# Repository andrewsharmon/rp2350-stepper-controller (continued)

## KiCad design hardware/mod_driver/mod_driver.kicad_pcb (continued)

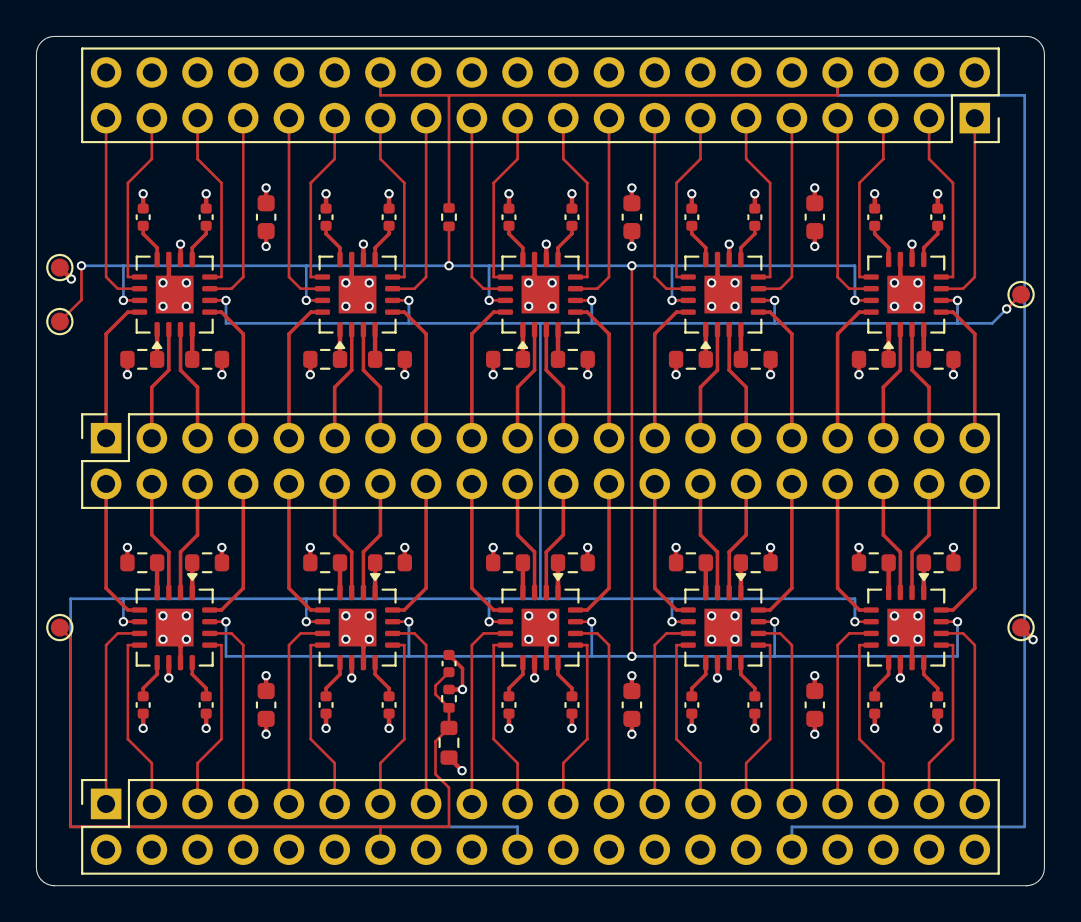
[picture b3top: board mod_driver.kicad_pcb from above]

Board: 4 copper layers, 56.0 x 47.2 mm, 68 parts (0 on the bottom side), 126 nets.

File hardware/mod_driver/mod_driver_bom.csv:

"Refs","Value","Footprint","Qty","MPN","LCSC","Note"
"C1,C4,C6,C9,C11,C14,C17,C19,C22,C24","1u","Capacitor_SMD:C_0402_1005Metric","10","CL05A105KA5NQNC","C52923",""
"C2,C5,C7,C10,C12,C15,C18,C20,C23,C25,C27","100n","Capacitor_SMD:C_0402_1005Metric","11","CL05B104KO5NNNC","C1525",""
"C3,C8,C13,C16,C21,C26","10u","Capacitor_SMD:C_0603_1608Metric","6","CL10A106KP8NNNC","C19702","VM, shared by the neighbouring drivers in the row; also the V5 bulk"
"J1","2x20 stacking","Connector_PinSocket_2.54mm:PinSocket_2x20_P2.54mm_Vertical","1","2.54-2*20PFemale longPC104","C35165","mod bus A (GPIO0-19 = M1-M5); passes through"
"J2","2x20 stacking","Connector_PinSocket_2.54mm:PinSocket_2x20_P2.54mm_Vertical","1","2.54-2*20PFemale longPC104","C35165","mod bus B (GPIO20-47); passes through"
"J3","2x20 stacking","Connector_PinSocket_2.54mm:PinSocket_2x20_P2.54mm_Vertical","1","2.54-2*20PFemale longPC104","C35165","motor outputs to mod_motor"
"R1-R20","1","Resistor_SMD:R_0603_1608Metric","20","0603WAF100KT5E","C22936","chops at 0.16-0.24 A (VTRIP 160-240 mV); Kelvin return"
"R21","47k","Resistor_SMD:R_0402_1005Metric","1","0402WGF4702TCE","C25792",""
"R22","39k 1%","Resistor_SMD:R_0603_1608Metric","1","0603WAF3902T5E","C23153",""
"R23","10k 1%","Resistor_SMD:R_0402_1005Metric","1","0402WGF1002TCE","C25744",""
"U1-U10","AT8833CQ","Package_DFN_QFN:QFN-16-1EP_4x4mm_P0.65mm_EP2.1x2.1mm","10","AT8833CQ","C5120769","DRV8833RTY pinout; 2nd source JSMSEMI DRV8833RTYR-JSM C55566425"

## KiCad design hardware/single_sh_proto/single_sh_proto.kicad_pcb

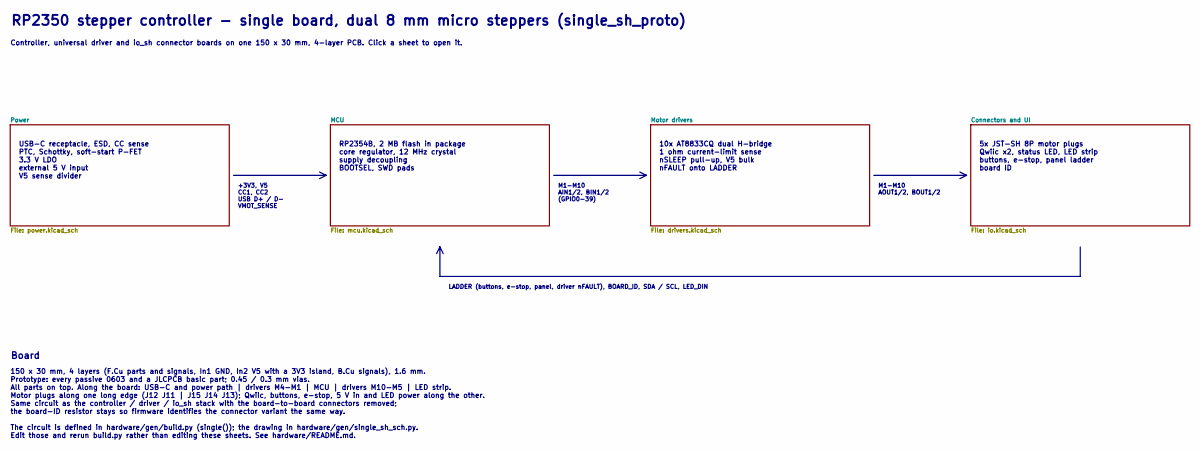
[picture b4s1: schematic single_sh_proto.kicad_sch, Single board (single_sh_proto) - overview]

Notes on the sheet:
RP2350 stepper controller - single board, dual 8 mm micro steppers (single_sh_proto)
Controller, universal driver and io_sh connector boards on one 150 x 30 mm, 4-layer PCB. Click a sheet to open it.
USB-C receptacle, ESD, CC sense PTC, Schottky, soft-start P-FET 3.3 V LDO external 5 V input V5 sense divider
RP2354B, 2 MB flash in package core regulator, 12 MHz crystal supply decoupling BOOTSEL, SWD pads
10x AT8833CQ dual H-bridge 1 ohm current-limit sense nSLEEP pull-up, V5 bulk nFAULT onto LADDER
5x JST-SH 8P motor plugs Qwiic x2, status LED, LED strip buttons, e-stop, panel ladder board ID
+3V3, V5 CC1, CC2 USB D+ / D- VMOT_SENSE
M1-M10 AIN1/2, BIN1/2 (GPIO0-39)
M1-M10 AOUT1/2, BOUT1/2
LADDER (buttons, e-stop, panel, driver nFAULT), BOARD_ID, SDA / SCL, LED_DIN
Board
150 x 30 mm, 4 layers (F.Cu parts and signals, In1 GND, In2 V5 with a 3V3 island, B.Cu signals), 1.6 mm. Prototype: every passive 0603 and a JLCPCB basic part; 0.45 / 0.3 mm vias. All parts on top. Along the board: USB-C and power path | drivers M4-M1 | MCU | drivers M10-M5 | LED strip. Motor plugs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

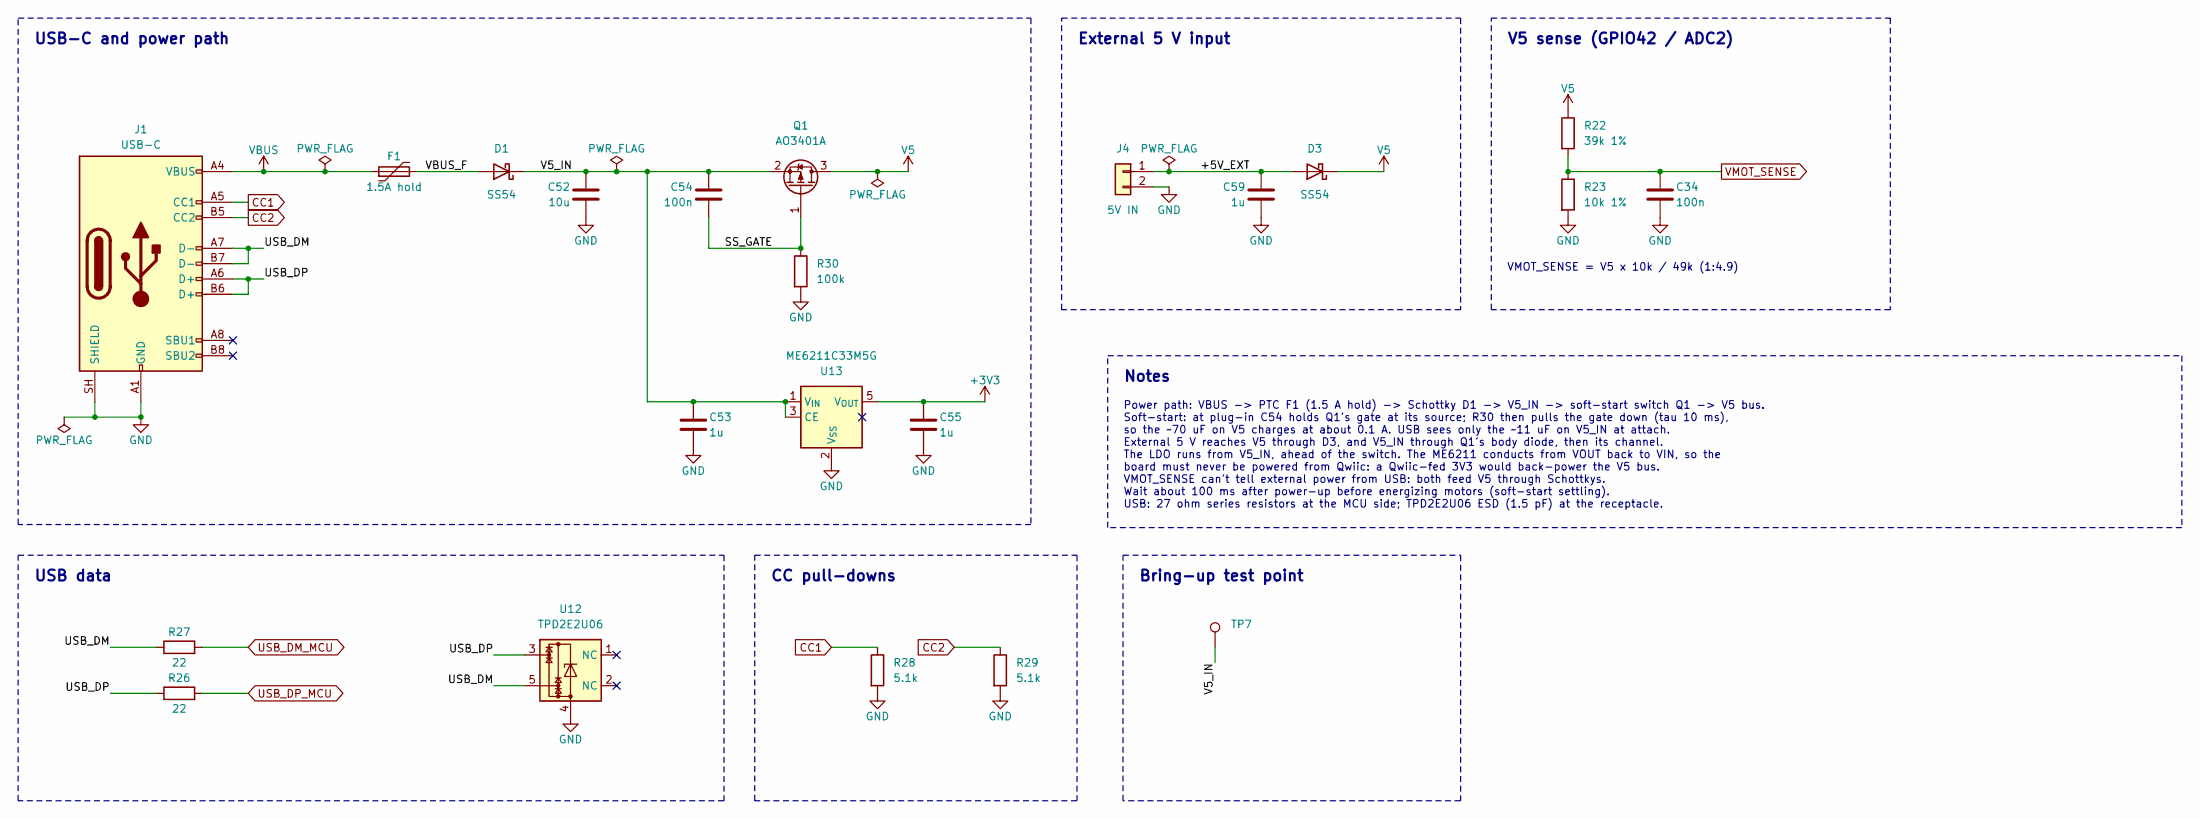
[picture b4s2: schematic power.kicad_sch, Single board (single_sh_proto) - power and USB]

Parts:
C34, C54: 100n; C_0603_1608Metric; MPN CC0603KRX7R9BB104; LCSC C14663
C52: 10u; C_0603_1608Metric; MPN CL10A106KP8NNNC; LCSC C19702
C53, C55, C59: 1u; C_0603_1608Metric; MPN CL10A105KB8NNNC; LCSC C15849
D1, D3: SS54; D_SMA; MPN SS54; LCSC C22452
F1: 1.5A hold; Fuse_1812_4532Metric; MPN SMD1812P150TF/8; LCSC C209721
J1: USB-C; USB_C_Receptacle_HRO_TYPE-C-31-M-12; MPN TYPE-C-31-M-12; LCSC C165948
J4: 5V IN; JST_PH_B2B-PH-K_1x02_P2.00mm_Vertical; MPN B2B-PH-K-S; LCSC C131337
Q1: AO3401A; SOT-23; MPN AO3401A; LCSC C15127
R22: 39k 1%; R_0603_1608Metric; MPN 0603WAF3902T5E; LCSC C23153
R23: 10k 1%; R_0603_1608Metric; MPN 0603WAF1002T5E; LCSC C25804
R26, R27: 22; R_0603_1608Metric; MPN 0603WAF220JT5E; LCSC C23345
R28, R29: 5.1k; R_0603_1608Metric; MPN 0603WAF5101T5E; LCSC C23186
R30: 100k; R_0603_1608Metric; MPN 0603WAF1003T5E; LCSC C25803
TP7: V5_IN; TestPoint_Pad_D1.0mm
U12: TPD2E2U06; SOT-553; MPN TPD2E2U06DRLR; LCSC C1972959
U13: ME6211C33M5G; SOT-23-5; MPN ME6211C33M5G-N; LCSC C82942

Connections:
+3V3: C55.1, U13.5 (V_{OUT}); also elsewhere on the board
/Power/+5V_EXT: C59.1, D3.2 (A), J4.1
/Power/SS_GATE: C54.2, Q1.1 (G), R30.1
/Power/USB_DM: J1.A7 (D-), J1.B7 (D-), R27.1, U12.5
/Power/USB_DP: J1.A6 (D+), J1.B6 (D+), R26.1, U12.3
/Power/V5_IN: C52.1, C53.1, C54.1, D1.1 (K), Q1.2 (S), TP7.1, U13.1 (V_{IN}), U13.3 (CE)
/Power/VBUS_F: D1.2 (A), F1.2
CC1: J1.A5 (CC1), R28.1; also elsewhere on the board
CC2: J1.B5 (CC2), R29.1; also elsewhere on the board
GND: C34.2, C52.2, C53.2, C55.2, C59.2, J1.A1 (GND), J1.A12 (GND), J1.B1 (GND), J1.B12 (GND), J1.SH (SHIELD), J4.2, R23.2, R28.2, R29.2, R30.2, U12.4, U13.2 (V_{SS}); also elsewhere on the board
USB_DM_MCU: R27.2; also elsewhere on the board
USB_DP_MCU: R26.2; also elsewhere on the board
V5: D3.1 (K), Q1.3 (D), R22.1; also elsewhere on the board
VBUS: F1.1, J1.A4 (VBUS), J1.A9 (VBUS), J1.B4 (VBUS), J1.B9 (VBUS); also elsewhere on the board
VMOT_SENSE: C34.1, R22.2, R23.1; also elsewhere on the board

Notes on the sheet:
USB-C and power path
USB data
CC pull-downs
External 5 V input
V5 sense (GPIO42 / ADC2)
VMOT_SENSE = V5 x 10k / 49k (1:4.9)
Notes
Power path: VBUS -> PTC F1 (1.5 A hold) -> Schottky D1 -> V5_IN -> soft-start switch Q1 -> V5 bus. Soft-start: at plug-in C54 holds Q1's gate at its source; R30 then pulls the gate down (tau 10 ms), so the ~70 uF on V5 charges at about 0.1 A. USB sees only the ~11 uF on V5_IN at attach. External 5 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
Bring-up test point

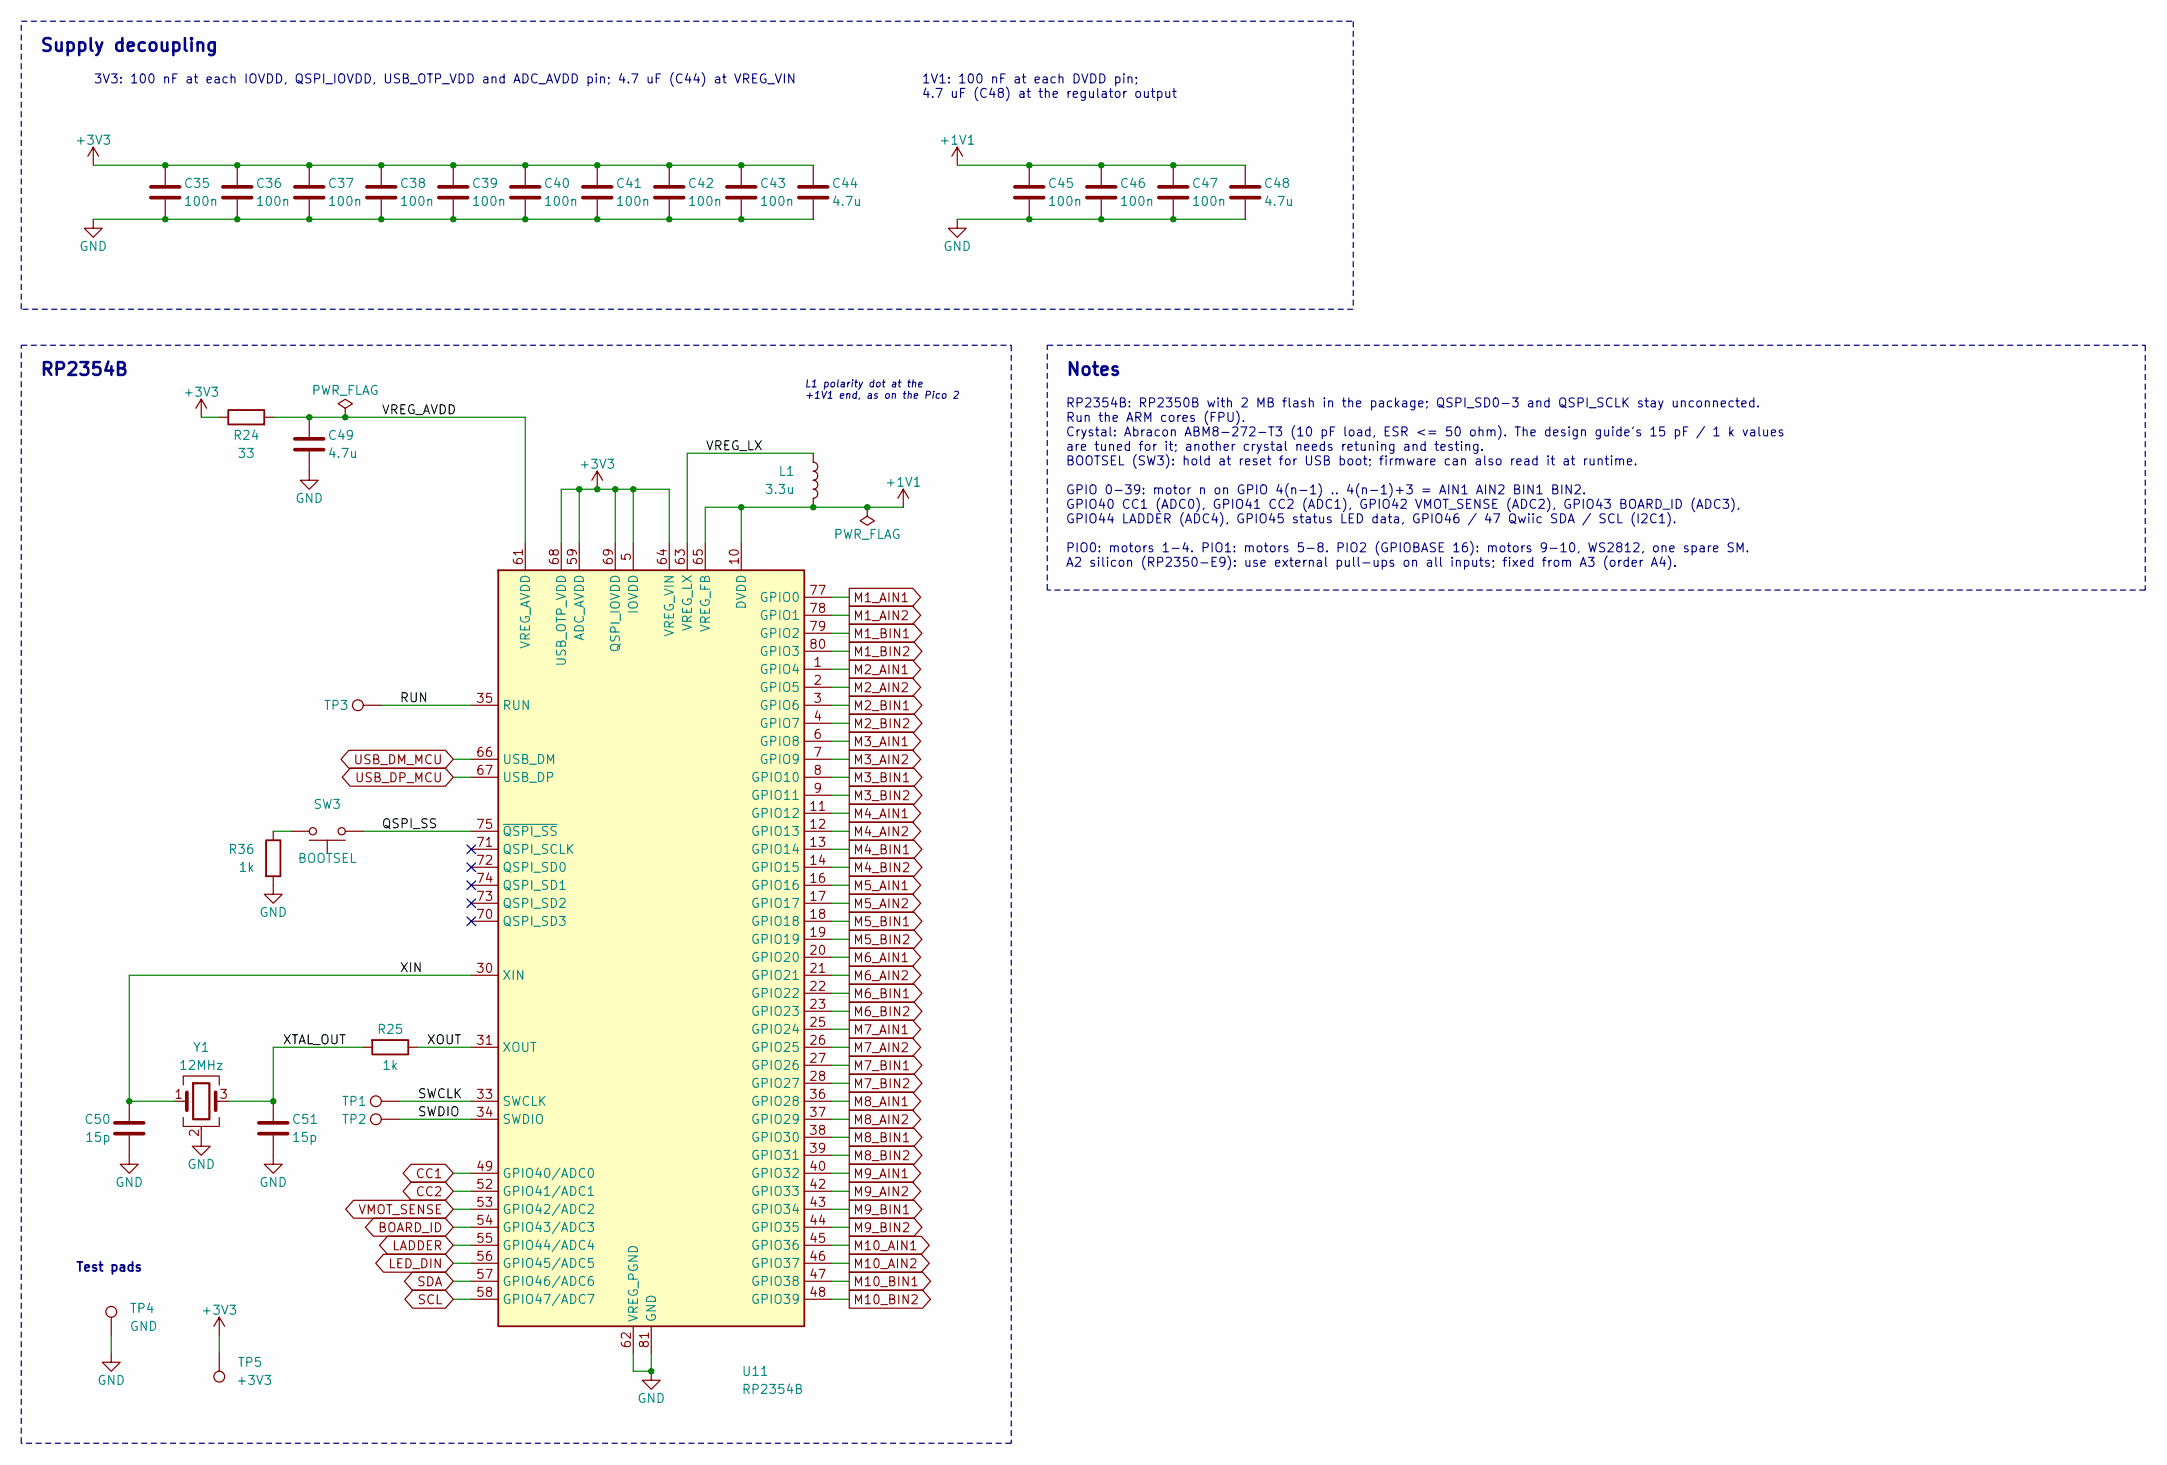
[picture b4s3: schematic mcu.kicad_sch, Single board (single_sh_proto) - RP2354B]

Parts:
C35, C36, C37, C38, C39, C40, C41, C42, C43, C45, C46, C47: 100n; C_0603_1608Metric; MPN CC0603KRX7R9BB104; LCSC C14663
C44, C48, C49: 4.7u; C_0603_1608Metric; MPN CL10A475KO8NNNC; LCSC C19666
C50, C51: 15p; C_0603_1608Metric; MPN CL10C150JB8NNNC; LCSC C1644
L1: 3.3u; L_Cenker_CKCS201610; MPN CMLW201610S3R3MST; LCSC C411344
R24: 33; R_0603_1608Metric; MPN 0603WAF330JT5E; LCSC C23140
R25, R36: 1k; R_0603_1608Metric; MPN 0603WAF1001T5E; LCSC C21190
SW3: BOOTSEL; SW_SPST_TS-1088-xR020; MPN TS-1088-AR02016; LCSC C720477
TP1: SWCLK; TestPoint_Pad_D1.0mm
TP2: SWDIO; TestPoint_Pad_D1.0mm
TP3: RUN; TestPoint_Pad_D1.0mm
TP4: GND; TestPoint_Pad_D1.0mm
TP5: +3V3; TestPoint_Pad_D1.0mm
U11: RP2354B; QFN-80-1EP_10x10mm_P0.4mm_EP3.4x3.4mm; MPN RP2354B; LCSC C39843328
Y1: 12MHz; Crystal_SMD_3225-4Pin_3.2x2.5mm; MPN ABM8-272-T3; LCSC C20625731

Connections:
+1V1: C45.1, C46.1, C47.1, C48.1, L1.2, U11.10 (DVDD), U11.32 (DVDD), U11.51 (DVDD), U11.65 (VREG_FB); also elsewhere on the board
+3V3: C35.1, C36.1, C37.1, C38.1, C39.1, C40.1, C41.1, C42.1, C43.1, C44.1, R24.1, TP5.1, U11.5 (IOVDD), U11.15 (IOVDD), U11.24 (IOVDD), U11.29 (IOVDD), U11.41 (IOVDD), U11.50 (IOVDD), U11.59 (ADC_AVDD), U11.60 (IOVDD), U11.64 (VREG_VIN), U11.68 (USB_OTP_VDD), U11.69 (QSPI_IOVDD), U11.76 (IOVDD); also elsewhere on the board
/MCU/QSPI_SS: SW3.1, U11.75 (~QSPI_SS)
/MCU/RUN: TP3.1, U11.35 (RUN)
/MCU/SWCLK: TP1.1, U11.33 (SWCLK)
/MCU/SWDIO: TP2.1, U11.34 (SWDIO)
/MCU/VREG_AVDD: C49.1, R24.2, U11.61 (VREG_AVDD)
/MCU/VREG_LX: L1.1, U11.63 (VREG_LX)
/MCU/XIN: C50.1, U11.30 (XIN), Y1.1
/MCU/XOUT: R25.1, U11.31 (XOUT)
/MCU/XTAL_OUT: C51.1, R25.2, Y1.3
BOARD_ID: U11.54 (GPIO43/ADC3); also elsewhere on the board
CC1: U11.49 (GPIO40/ADC0); also elsewhere on the board
CC2: U11.52 (GPIO41/ADC1); also elsewhere on the board
GND: C35.2, C36.2, C37.2, C38.2, C39.2, C40.2, C41.2, C42.2, C43.2, C44.2, C45.2, C46.2, C47.2, C48.2, C49.2, C50.2, C51.2, R36.2, TP4.1, U11.62 (VREG_PGND), U11.81 (GND), Y1.2 (G), Y1.4 (G); also elsewhere on the board
LADDER: U11.55 (GPIO44/ADC4); also elsewhere on the board
LED_DIN: U11.56 (GPIO45/ADC5); also elsewhere on the board
M1_AIN1: U11.77 (GPIO0); also elsewhere on the board
M1_AIN2: U11.78 (GPIO1); also elsewhere on the board
M1_BIN1: U11.79 (GPIO2); also elsewhere on the board
M1_BIN2: U11.80 (GPIO3); also elsewhere on the board
M2_AIN1: U11.1 (GPIO4); also elsewhere on the board
M2_AIN2: U11.2 (GPIO5); also elsewhere on the board
M2_BIN1: U11.3 (GPIO6); also elsewhere on the board
M2_BIN2: U11.4 (GPIO7); also elsewhere on the board
M3_AIN1: U11.6 (GPIO8); also elsewhere on the board
M3_AIN2: U11.7 (GPIO9); also elsewhere on the board
M3_BIN1: U11.8 (GPIO10); also elsewhere on the board
M3_BIN2: U11.9 (GPIO11); also elsewhere on the board
M4_AIN1: U11.11 (GPIO12); also elsewhere on the board
M4_AIN2: U11.12 (GPIO13); also elsewhere on the board
M4_BIN1: U11.13 (GPIO14); also elsewhere on the board
M4_BIN2: U11.14 (GPIO15); also elsewhere on the board
M5_AIN1: U11.16 (GPIO16); also elsewhere on the board
M5_AIN2: U11.17 (GPIO17); also elsewhere on the board
M5_BIN1: U11.18 (GPIO18); also elsewhere on the board
M5_BIN2: U11.19 (GPIO19); also elsewhere on the board
M6_AIN1: U11.20 (GPIO20); also elsewhere on the board
M6_AIN2: U11.21 (GPIO21); also elsewhere on the board
M6_BIN1: U11.22 (GPIO22); also elsewhere on the board
M6_BIN2: U11.23 (GPIO23); also elsewhere on the board
M7_AIN1: U11.25 (GPIO24); also elsewhere on the board
M7_AIN2: U11.26 (GPIO25); also elsewhere on the board
M7_BIN1: U11.27 (GPIO26); also elsewhere on the board
M7_BIN2: U11.28 (GPIO27); also elsewhere on the board
M8_AIN1: U11.36 (GPIO28); also elsewhere on the board
M8_AIN2: U11.37 (GPIO29); also elsewhere on the board
M8_BIN1: U11.38 (GPIO30); also elsewhere on the board
M8_BIN2: U11.39 (GPIO31); also elsewhere on the board
M9_AIN1: U11.40 (GPIO32); also elsewhere on the board
M9_AIN2: U11.42 (GPIO33); also elsewhere on the board
M9_BIN1: U11.43 (GPIO34); also elsewhere on the board
M9_BIN2: U11.44 (GPIO35); also elsewhere on the board
M10_AIN1: U11.45 (GPIO36); also elsewhere on the board
M10_AIN2: U11.46 (GPIO37); also elsewhere on the board
M10_BIN1: U11.47 (GPIO38); also elsewhere on the board
M10_BIN2: U11.48 (GPIO39); also elsewhere on the board
unnamed: R36.1, SW3.2
SCL: U11.58 (GPIO47/ADC7); also elsewhere on the board
SDA: U11.57 (GPIO46/ADC6); also elsewhere on the board
USB_DM_MCU: U11.66 (USB_DM); also elsewhere on the board
USB_DP_MCU: U11.67 (USB_DP); also elsewhere on the board
VMOT_SENSE: U11.53 (GPIO42/ADC2); also elsewhere on the board

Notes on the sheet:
RP2354B
L1 polarity dot at the +1V1 end, as on the Pico 2
Supply decoupling
3V3: 100 nF at each IOVDD, QSPI_IOVDD, USB_OTP_VDD and ADC_AVDD pin; 4.7 uF (C44) at VREG_VIN
1V1: 100 nF at each DVDD pin; 4.7 uF (C48) at the regulator output
Test pads
Notes
RP2354B: RP2350B with 2 MB flash in the package; QSPI_SD0-3 and QSPI_SCLK stay unconnected. Run the ARM cores (FPU). Crystal: Abracon ABM8-272-T3 (10 pF load, ESR <= 50 ohm). The design guide's 15 pF / 1 k values are tuned for it; another crystal needs retuning and testing. BOOTSEL (SW3): hold at r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

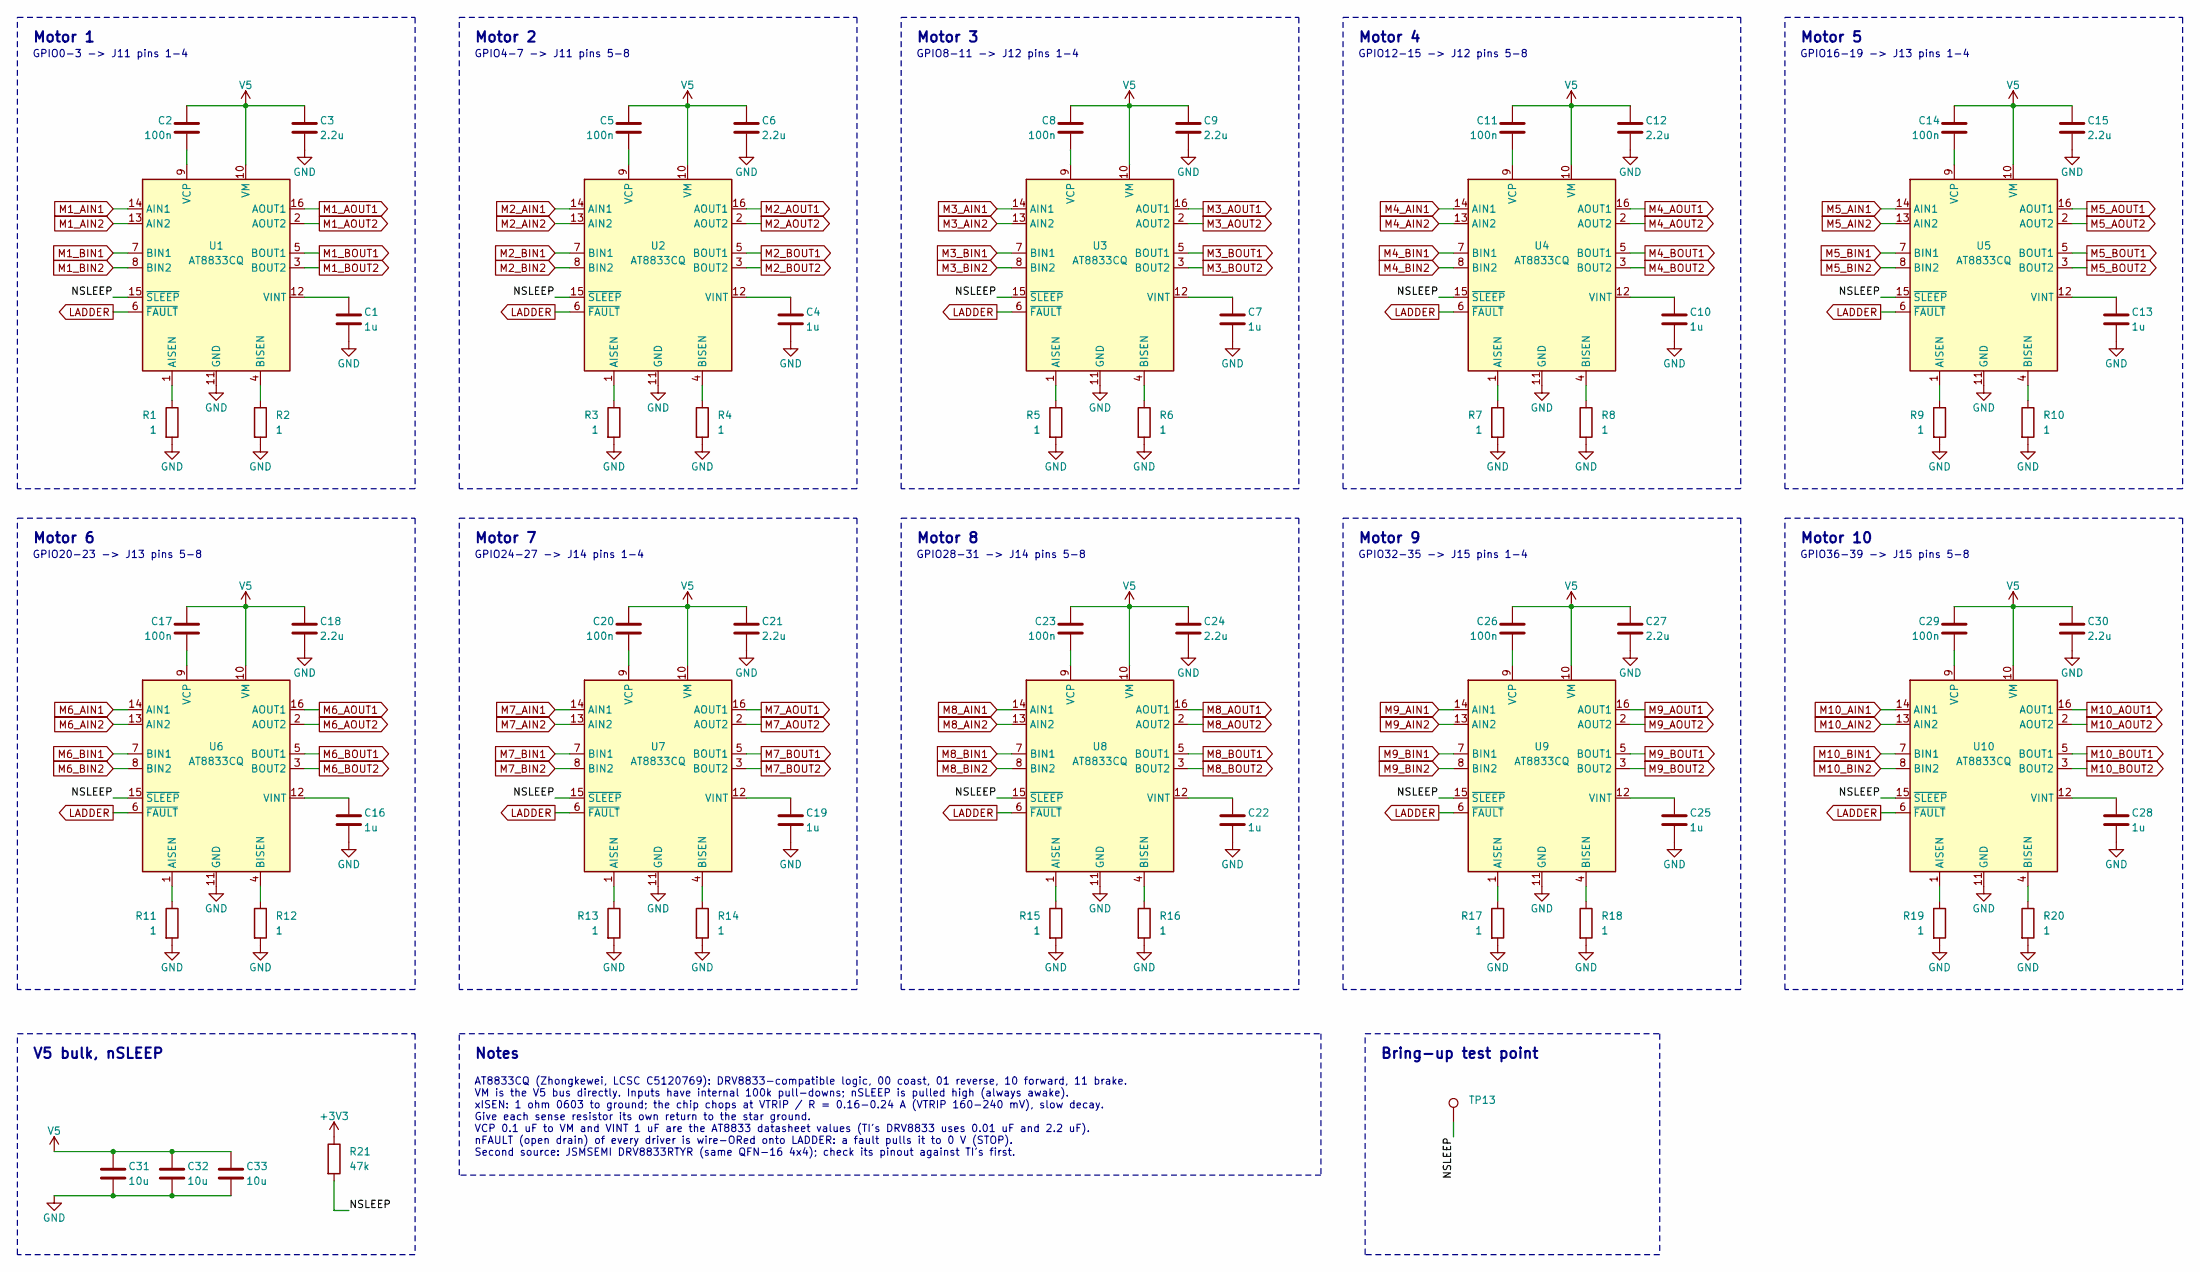
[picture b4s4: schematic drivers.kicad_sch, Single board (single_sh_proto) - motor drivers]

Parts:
C1, C4, C7, C10, C13, C16, C19, C22, C25, C28: 1u; C_0603_1608Metric; MPN CL10A105KB8NNNC; LCSC C15849
C2, C5, C8, C11, C14, C17, C20, C23, C26, C29: 100n; C_0603_1608Metric; MPN CC0603KRX7R9BB104; LCSC C14663
C3, C6, C9, C12, C15, C18, C21, C24, C27, C30: 2.2u; C_0603_1608Metric; MPN CL10A225KO8NNNC; LCSC C23630
C31, C32, C33: 10u; C_0603_1608Metric; MPN CL10A106KP8NNNC; LCSC C19702
R1, R2, R3, R4, R5, R6, R7, R8, R9, R10, R11, R12, R13, R14, R15, R16, R17, R18, R19, R20: 1; R_0603_1608Metric; MPN 0603WAF100KT5E; LCSC C22936
R21: 47k; R_0603_1608Metric; MPN 0603WAF4702T5E; LCSC C25819
TP13: NSLEEP; TestPoint_Pad_D1.0mm
U1, U2, U3, U4, U5, U6, U7, U8, U9, U10: AT8833CQ; QFN-16-1EP_4x4mm_P0.65mm_EP2.1x2.1mm; MPN AT8833CQ; LCSC C5120769

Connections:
+3V3: R21.1; also elsewhere on the board
/Motor drivers/NSLEEP: R21.2, TP13.1, U1.15 (~SLEEP), U2.15 (~SLEEP), U3.15 (~SLEEP), U4.15 (~SLEEP), U5.15 (~SLEEP), U6.15 (~SLEEP), U7.15 (~SLEEP), U8.15 (~SLEEP), U9.15 (~SLEEP), U10.15 (~SLEEP)
GND: C1.2, C3.2, C4.2, C6.2, C7.2, C9.2, C10.2, C12.2, C13.2, C15.2, C16.2, C18.2, C19.2, C21.2, C22.2, C24.2, C25.2, C27.2, C28.2, C30.2, C31.2, C32.2, C33.2, R1.2, R2.2, R3.2, R4.2, R5.2, R6.2, R7.2, R8.2, R9.2, R10.2, R11.2, R12.2, R13.2, R14.2, R15.2, R16.2, R17.2, R18.2, R19.2, R20.2, U1.11 (GND), U1.17 (GND), U2.11 (GND), U2.17 (GND), U3.11 (GND), U3.17 (GND), U4.11 (GND), U4.17 (GND), U5.11 (GND), U5.17 (GND), U6.11 (GND), U6.17 (GND), U7.11 (GND), U7.17 (GND), U8.11 (GND), U8.17 (GND), U9.11 (GND), U9.17 (GND), U10.11 (GND), U10.17 (GND); also elsewhere on the board
LADDER: U1.6 (~FAULT), U2.6 (~FAULT), U3.6 (~FAULT), U4.6 (~FAULT), U5.6 (~FAULT), U6.6 (~FAULT), U7.6 (~FAULT), U8.6 (~FAULT), U9.6 (~FAULT), U10.6 (~FAULT); also elsewhere on the board
M1_AIN1: U1.14 (AIN1); also elsewhere on the board
M1_AIN2: U1.13 (AIN2); also elsewhere on the board
M1_AOUT1: U1.16 (AOUT1); also elsewhere on the board
M1_AOUT2: U1.2 (AOUT2); also elsewhere on the board
M1_BIN1: U1.7 (BIN1); also elsewhere on the board
M1_BIN2: U1.8 (BIN2); also elsewhere on the board
M1_BOUT1: U1.5 (BOUT1); also elsewhere on the board
M1_BOUT2: U1.3 (BOUT2); also elsewhere on the board
M2_AIN1: U2.14 (AIN1); also elsewhere on the board
M2_AIN2: U2.13 (AIN2); also elsewhere on the board
M2_AOUT1: U2.16 (AOUT1); also elsewhere on the board
M2_AOUT2: U2.2 (AOUT2); also elsewhere on the board
M2_BIN1: U2.7 (BIN1); also elsewhere on the board
M2_BIN2: U2.8 (BIN2); also elsewhere on the board
M2_BOUT1: U2.5 (BOUT1); also elsewhere on the board
M2_BOUT2: U2.3 (BOUT2); also elsewhere on the board
M3_AIN1: U3.14 (AIN1); also elsewhere on the board
M3_AIN2: U3.13 (AIN2); also elsewhere on the board
M3_AOUT1: U3.16 (AOUT1); also elsewhere on the board
M3_AOUT2: U3.2 (AOUT2); also elsewhere on the board
M3_BIN1: U3.7 (BIN1); also elsewhere on the board
M3_BIN2: U3.8 (BIN2); also elsewhere on the board
M3_BOUT1: U3.5 (BOUT1); also elsewhere on the board
M3_BOUT2: U3.3 (BOUT2); also elsewhere on the board
M4_AIN1: U4.14 (AIN1); also elsewhere on the board
M4_AIN2: U4.13 (AIN2); also elsewhere on the board
M4_AOUT1: U4.16 (AOUT1); also elsewhere on the board
M4_AOUT2: U4.2 (AOUT2); also elsewhere on the board
M4_BIN1: U4.7 (BIN1); also elsewhere on the board
M4_BIN2: U4.8 (BIN2); also elsewhere on the board
M4_BOUT1: U4.5 (BOUT1); also elsewhere on the board
M4_BOUT2: U4.3 (BOUT2); also elsewhere on the board
M5_AIN1: U5.14 (AIN1); also elsewhere on the board
M5_AIN2: U5.13 (AIN2); also elsewhere on the board
M5_AOUT1: U5.16 (AOUT1); also elsewhere on the board
M5_AOUT2: U5.2 (AOUT2); also elsewhere on the board
M5_BIN1: U5.7 (BIN1); also elsewhere on the board
M5_BIN2: U5.8 (BIN2); also elsewhere on the board
M5_BOUT1: U5.5 (BOUT1); also elsewhere on the board
M5_BOUT2: U5.3 (BOUT2); also elsewhere on the board
M6_AIN1: U6.14 (AIN1); also elsewhere on the board
M6_AIN2: U6.13 (AIN2); also elsewhere on the board
M6_AOUT1: U6.16 (AOUT1); also elsewhere on the board
M6_AOUT2: U6.2 (AOUT2); also elsewhere on the board
M6_BIN1: U6.7 (BIN1); also elsewhere on the board
M6_BIN2: U6.8 (BIN2); also elsewhere on the board
M6_BOUT1: U6.5 (BOUT1); also elsewhere on the board
M6_BOUT2: U6.3 (BOUT2); also elsewhere on the board
M7_AIN1: U7.14 (AIN1); also elsewhere on the board
M7_AIN2: U7.13 (AIN2); also elsewhere on the board
M7_AOUT1: U7.16 (AOUT1); also elsewhere on the board
M7_AOUT2: U7.2 (AOUT2); also elsewhere on the board
M7_BIN1: U7.7 (BIN1); also elsewhere on the board
M7_BIN2: U7.8 (BIN2); also elsewhere on the board
M7_BOUT1: U7.5 (BOUT1); also elsewhere on the board
M7_BOUT2: U7.3 (BOUT2); also elsewhere on the board
M8_AIN1: U8.14 (AIN1); also elsewhere on the board
M8_AIN2: U8.13 (AIN2); also elsewhere on the board
M8_AOUT1: U8.16 (AOUT1); also elsewhere on the board
M8_AOUT2: U8.2 (AOUT2); also elsewhere on the board
M8_BIN1: U8.7 (BIN1); also elsewhere on the board
M8_BIN2: U8.8 (BIN2); also elsewhere on the board
M8_BOUT1: U8.5 (BOUT1); also elsewhere on the board
M8_BOUT2: U8.3 (BOUT2); also elsewhere on the board
M9_AIN1: U9.14 (AIN1); also elsewhere on the board
M9_AIN2: U9.13 (AIN2); also elsewhere on the board
M9_AOUT1: U9.16 (AOUT1); also elsewhere on the board
M9_AOUT2: U9.2 (AOUT2); also elsewhere on the board
M9_BIN1: U9.7 (BIN1); also elsewhere on the board
M9_BIN2: U9.8 (BIN2); also elsewhere on the board
M9_BOUT1: U9.5 (BOUT1); also elsewhere on the board
M9_BOUT2: U9.3 (BOUT2); also elsewhere on the board
M10_AIN1: U10.14 (AIN1); also elsewhere on the board
M10_AIN2: U10.13 (AIN2); also elsewhere on the board
M10_AOUT1: U10.16 (AOUT1); also elsewhere on the board
M10_AOUT2: U10.2 (AOUT2); also elsewhere on the board
M10_BIN1: U10.7 (BIN1); also elsewhere on the board
M10_BIN2: U10.8 (BIN2); also elsewhere on the board
M10_BOUT1: U10.5 (BOUT1); also elsewhere on the board
M10_BOUT2: U10.3 (BOUT2); also elsewhere on the board
unnamed: R1.1, U1.1 (AISEN)
unnamed: R2.1, U1.4 (BISEN)
unnamed: C2.1, U1.9 (VCP)
unnamed: C1.1, U1.12 (VINT)
unnamed: R3.1, U2.1 (AISEN)
unnamed: R4.1, U2.4 (BISEN)
unnamed: C5.1, U2.9 (VCP)
unnamed: C4.1, U2.12 (VINT)
unnamed: R5.1, U3.1 (AISEN)
unnamed: R6.1, U3.4 (BISEN)
unnamed: C8.1, U3.9 (VCP)
unnamed: C7.1, U3.12 (VINT)
unnamed: R7.1, U4.1 (AISEN)
unnamed: R8.1, U4.4 (BISEN)
unnamed: C11.1, U4.9 (VCP)
unnamed: C10.1, U4.12 (VINT)
unnamed: R9.1, U5.1 (AISEN)
unnamed: R10.1, U5.4 (BISEN)
unnamed: C14.1, U5.9 (VCP)
unnamed: C13.1, U5.12 (VINT)
unnamed: R11.1, U6.1 (AISEN)
unnamed: R12.1, U6.4 (BISEN)
unnamed: C17.1, U6.9 (VCP)
unnamed: C16.1, U6.12 (VINT)
unnamed: R13.1, U7.1 (AISEN)
unnamed: R14.1, U7.4 (BISEN)
unnamed: C20.1, U7.9 (VCP)
unnamed: C19.1, U7.12 (VINT)
unnamed: R15.1, U8.1 (AISEN)
unnamed: R16.1, U8.4 (BISEN)
unnamed: C23.1, U8.9 (VCP)
unnamed: C22.1, U8.12 (VINT)
unnamed: R17.1, U9.1 (AISEN)
unnamed: R18.1, U9.4 (BISEN)
unnamed: C26.1, U9.9 (VCP)
unnamed: C25.1, U9.12 (VINT)
unnamed: R19.1, U10.1 (AISEN)
unnamed: R20.1, U10.4 (BISEN)
unnamed: C29.1, U10.9 (VCP)
unnamed: C28.1, U10.12 (VINT)
V5: C2.2, C3.1, C5.2, C6.1, C8.2, C9.1, C11.2, C12.1, C14.2, C15.1, C17.2, C18.1, C20.2, C21.1, C23.2, C24.1, C26.2, C27.1, C29.2, C30.1, C31.1, C32.1, C33.1, U1.10 (VM), U2.10 (VM), U3.10 (VM), U4.10 (VM), U5.10 (VM), U6.10 (VM), U7.10 (VM), U8.10 (VM), U9.10 (VM), U10.10 (VM); also elsewhere on the board

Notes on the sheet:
Motor 1
GPIO0-3 -> J11 pins 1-4
Motor 2
GPIO4-7 -> J11 pins 5-8
Motor 3
GPIO8-11 -> J12 pins 1-4
Motor 4
GPIO12-15 -> J12 pins 5-8
Motor 5
GPIO16-19 -> J13 pins 1-4
Motor 6
GPIO20-23 -> J13 pins 5-8
Motor 7
GPIO24-27 -> J14 pins 1-4
Motor 8
GPIO28-31 -> J14 pins 5-8
Motor 9
GPIO32-35 -> J15 pins 1-4
Motor 10
GPIO36-39 -> J15 pins 5-8
V5 bulk, nSLEEP
Notes
AT8833CQ (Zhongkewei, LCSC C5120769): DRV8833-compatible logic, 00 coast, 01 reverse, 10 forward, 11 brake. VM is the V5 bus directly. Inputs have internal 100k pull-downs; nSLEEP is pulled high (always awake). xISEN: 1 ohm 0603 to ground; the chip chops at VTRIP / R = 0.16-0.24 A (VTRIP 160-240 mV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
Bring-up test point
